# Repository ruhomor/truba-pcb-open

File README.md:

# Palka project

Some documentation [here](documentation.md)

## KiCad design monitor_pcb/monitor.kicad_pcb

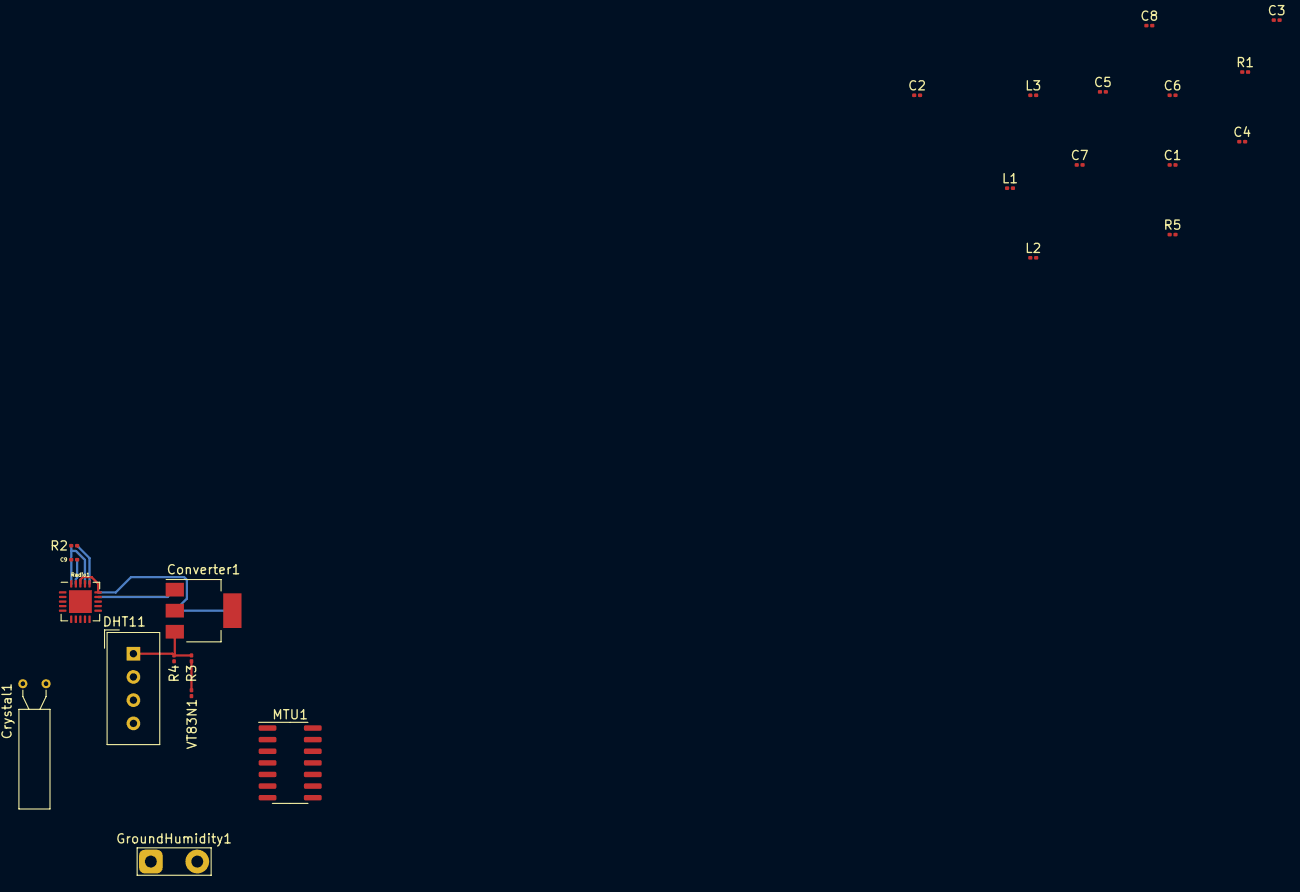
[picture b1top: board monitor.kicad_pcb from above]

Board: 2 copper layers, 24 parts (0 on the bottom side), 20 nets.

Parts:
C1: 4.7pF; C_0201_0603Metric
C2: 1.5pF; C_0201_0603Metric
C3: 1pF; C_0201_0603Metric
C4: 2.2nF; C_0201_0603Metric
C5, C6: 22pF; C_0201_0603Metric
C7: 1nF; C_0201_0603Metric
C8: 10nF; C_0201_0603Metric
C9: 33nF; C_0201_0603Metric
Converter1: AMS1117-3.3; SOT-223-3_TabPin2
Crystal1: 16MHz; Crystal_AT310_D3.0mm_L10.0mm_Horizontal
DHT11: DHT11; Aosong_DHT11_5.5x12.0_P2.54mm
GroundHumidity1: GroundHumidity; TestPoint_2Pads_Pitch5.08mm_Drill1.3mm
L1: 2.7nH; L_0201_0603Metric
L2: 3.9nH; L_0201_0603Metric
L3: 8.2nH; L_0201_0603Metric
MTU1: ATtiny24A-SS; SOIC-14_3.9x8.7mm_P1.27mm
R1: 1M; R_0201_0603Metric
R2: 22k; R_0201_0603Metric
R3, R4, R5: 10k; R_0201_0603Metric
Radio1: NRF24L01; QFN-20-1EP_4x4mm_P0.5mm_EP2.5x2.5mm
VT83N1: R_Photo; R_0201_0603Metric

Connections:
50 Ohm RFI/O: C2.2, C3.1
+5V: Converter1.3 (VI), DHT11.1 (VCC), GroundHumidity1.2, MTU1.1 (VCC), R3.2, R4.1
GND: C1.1, C3.2, C4.1, C5.2, C6.2, C7.2, C8.2, C9.2, Converter1.1 (GND), DHT11.4 (GND), MTU1.14 (GND), R2.2, R5.2, Radio1.8 (VSS), Radio1.14 (VSS), Radio1.17 (VSS), Radio1.20 (VSS), VT83N1.2
unnamed: C1.2, C4.2, L1.2, Radio1.11 (VDD_PA)
unnamed: C2.1, L2.2
unnamed: C5.1, Crystal1.2, R1.1, Radio1.10 (XC1)
unnamed: C6.1, Crystal1.1, R1.2, Radio1.9 (XC2)
unnamed: C7.1, C8.1, Converter1.2 (VO), Radio1.7 (VDD), Radio1.15 (VDD), Radio1.18 (VDD)
unnamed: C9.1, Radio1.19 (DVDD)
unnamed: DHT11.2 (IO), MTU1.13 (AREF/PA0), R4.2
unnamed: GroundHumidity1.1, MTU1.6 (PA7), R5.1
unnamed: L1.1, L3.1, Radio1.12 (ANT1)
unnamed: L2.1, L3.2, Radio1.13 (ANT2)
unnamed: MTU1.7 (PA6), Radio1.4 (MOSI)
unnamed: MTU1.8 (PA5), Radio1.5 (MISO)
unnamed: MTU1.9 (PA4), Radio1.3 (SCK)
unnamed: MTU1.10 (PA3), Radio1.2 (CSN)
unnamed: MTU1.11 (PA2), Radio1.1 (CE)
unnamed: MTU1.12 (PA1), R3.1, VT83N1.1
unnamed: R2.1, Radio1.16 (IREF)

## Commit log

2023-05-15 move project files
